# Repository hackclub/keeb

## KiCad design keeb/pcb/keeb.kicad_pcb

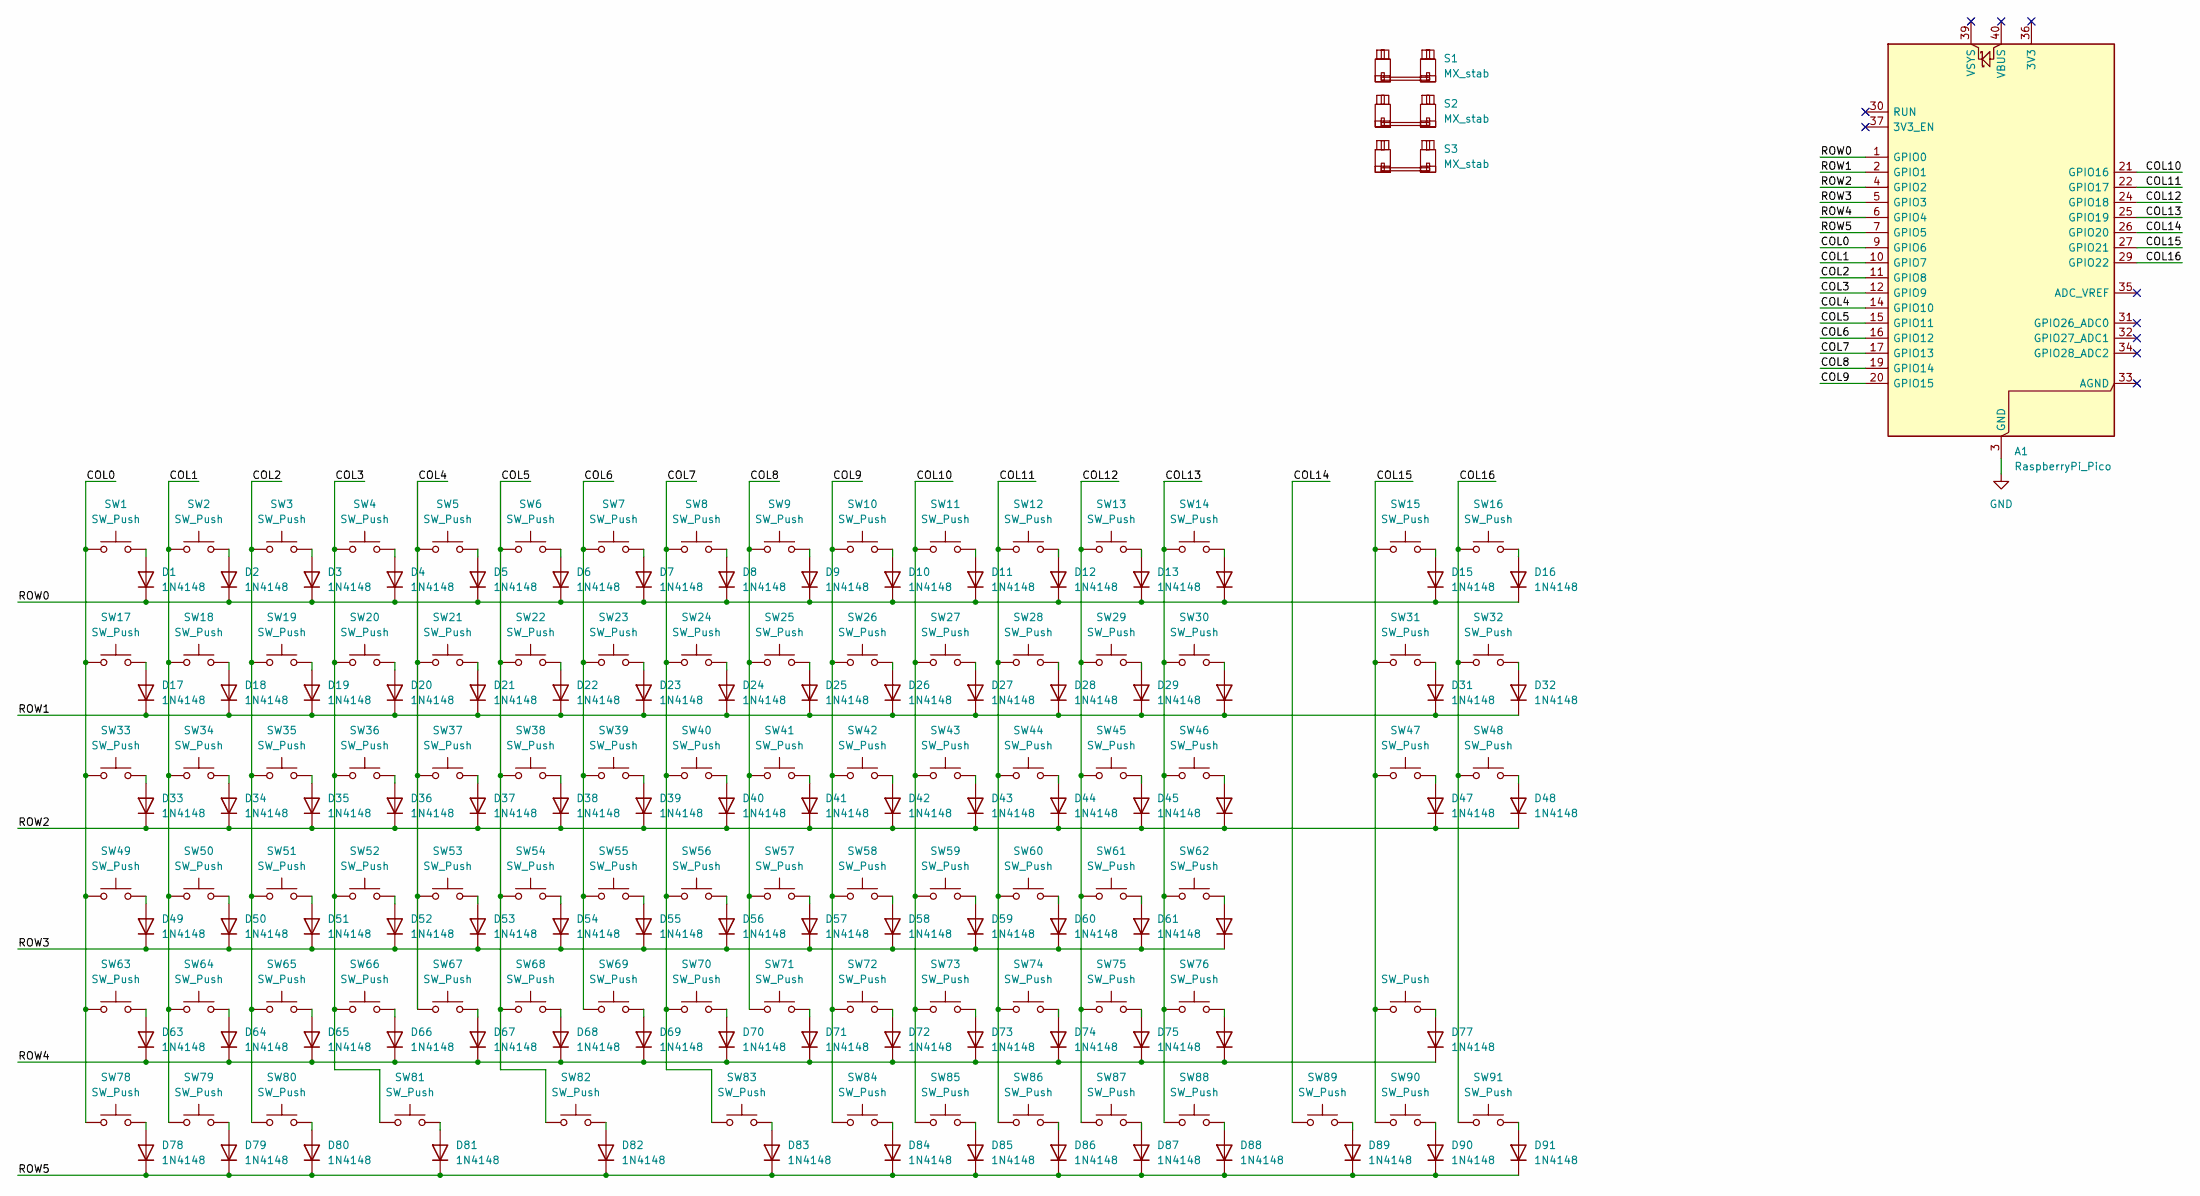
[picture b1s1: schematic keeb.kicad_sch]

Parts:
A1: RaspberryPi_Pico; RaspberryPi_Pico_Common_SMD
D1, D2, D3, D4, D5, D6, D7, D8, D9, D10, D11, D12, D13, D14, D15, D16, D17, D18, D19, D20, D21, D22, D23, D24, D25, D26, D27, D28, D29, D30, D31, D32, D33, D34, D35, D36, D37, D38, D39, D40, D41, D42, D43, D44, D45, D46, D47, D48, D49, D50, D51, D52, D53, D54, D55, D56, D57, D58, D59, D60, D61, D62, D63, D64, D65, D66, D67, D68, D69, D70, D71, D72, D73, D74, D75, D76, D77, D78, D79, D80, D81, D82, D83, D84, D85, D86, D87, D88, D89, D90, D91: 1N4148; D_DO-35_SOD27_P7.62mm_Horizontal
S1, S2, S3: MX_stab; STAB_MX_2u
SW1, SW2, SW3, SW4, SW5, SW6, SW7, SW8, SW9, SW10, SW11, SW12, SW13, SW14, SW15, SW16, SW17, SW18, SW19, SW20, SW21, SW22, SW23, SW24, SW25, SW26, SW27, SW28, SW29, SW30, SW31, SW32, SW33, SW34, SW35, SW36, SW37, SW38, SW39, SW40, SW41, SW42, SW43, SW44, SW45, SW46, SW47, SW48, SW49, SW50, SW51, SW52, SW53, SW54, SW55, SW56, SW57, SW58, SW59, SW60, SW61, SW62, SW63, SW64, SW65, SW66, SW67, SW68, SW69, SW70, SW71, SW72, SW73, SW74, SW75, SW76, SW77, SW78, SW79, SW80, SW81, SW82, SW83, SW84, SW85, SW86, SW87, SW88, SW89, SW90, SW91: SW_Push; SW_MX_1u

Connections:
/COL0: A1.9 (GPIO6), SW1.1, SW17.1, SW33.1, SW49.1, SW63.1, SW78.1
/COL1: A1.10 (GPIO7), SW2.1, SW18.1, SW34.1, SW50.1, SW64.1, SW79.1
/COL2: A1.11 (GPIO8), SW3.1, SW19.1, SW35.1, SW51.1, SW65.1, SW80.1
/COL3: A1.12 (GPIO9), SW4.1, SW20.1, SW36.1, SW52.1, SW66.1, SW81.1
/COL4: A1.14 (GPIO10), SW5.1, SW21.1, SW37.1, SW53.1, SW67.1
/COL5: A1.15 (GPIO11), SW6.1, SW22.1, SW38.1, SW54.1, SW68.1, SW82.1
/COL6: A1.16 (GPIO12), SW7.1, SW23.1, SW39.1, SW55.1, SW69.1
/COL7: A1.17 (GPIO13), SW8.1, SW24.1, SW40.1, SW56.1, SW70.1, SW83.1
/COL8: A1.19 (GPIO14), SW9.1, SW25.1, SW41.1, SW57.1, SW71.1
/COL9: A1.20 (GPIO15), SW10.1, SW26.1, SW42.1, SW58.1, SW72.1, SW84.1
/COL10: A1.21 (GPIO16), SW11.1, SW27.1, SW43.1, SW59.1, SW73.1, SW85.1
/COL11: A1.22 (GPIO17), SW12.1, SW28.1, SW44.1, SW60.1, SW74.1, SW86.1
/COL12: A1.24 (GPIO18), SW13.1, SW29.1, SW45.1, SW61.1, SW75.1, SW87.1
/COL13: A1.25 (GPIO19), SW14.1, SW30.1, SW46.1, SW62.1, SW76.1, SW88.1
/COL14: A1.26 (GPIO20), SW89.1
/COL15: A1.27 (GPIO21), SW15.1, SW31.1, SW47.1, SW77.1, SW90.1
/COL16: A1.29 (GPIO22), SW16.1, SW32.1, SW48.1, SW91.1
/ROW0: A1.1 (GPIO0), D1.1 (K), D2.1 (K), D3.1 (K), D4.1 (K), D5.1 (K), D6.1 (K), D7.1 (K), D8.1 (K), D9.1 (K), D10.1 (K), D11.1 (K), D12.1 (K), D13.1 (K), D14.1 (K), D15.1 (K), D16.1 (K)
/ROW1: A1.2 (GPIO1), D17.1 (K), D18.1 (K), D19.1 (K), D20.1 (K), D21.1 (K), D22.1 (K), D23.1 (K), D24.1 (K), D25.1 (K), D26.1 (K), D27.1 (K), D28.1 (K), D29.1 (K), D30.1 (K), D31.1 (K), D32.1 (K)
/ROW2: A1.4 (GPIO2), D33.1 (K), D34.1 (K), D35.1 (K), D36.1 (K), D37.1 (K), D38.1 (K), D39.1 (K), D40.1 (K), D41.1 (K), D42.1 (K), D43.1 (K), D44.1 (K), D45.1 (K), D46.1 (K), D47.1 (K), D48.1 (K)
/ROW3: A1.5 (GPIO3), D49.1 (K), D50.1 (K), D51.1 (K), D52.1 (K), D53.1 (K), D54.1 (K), D55.1 (K), D56.1 (K), D57.1 (K), D58.1 (K), D59.1 (K), D60.1 (K), D61.1 (K), D62.1 (K)
/ROW4: A1.6 (GPIO4), D63.1 (K), D64.1 (K), D65.1 (K), D66.1 (K), D67.1 (K), D68.1 (K), D69.1 (K), D70.1 (K), D71.1 (K), D72.1 (K), D73.1 (K), D74.1 (K), D75.1 (K), D76.1 (K), D77.1 (K)
/ROW5: A1.7 (GPIO5), D78.1 (K), D79.1 (K), D80.1 (K), D81.1 (K), D82.1 (K), D83.1 (K), D84.1 (K), D85.1 (K), D86.1 (K), D87.1 (K), D88.1 (K), D89.1 (K), D90.1 (K), D91.1 (K)
GND: A1.3 (GND), A1.8 (GND), A1.13 (GND), A1.18 (GND), A1.23 (GND), A1.28 (GND), A1.38 (GND)
unnamed: D1.2 (A), SW1.2
unnamed: D2.2 (A), SW2.2
unnamed: D3.2 (A), SW3.2
unnamed: D4.2 (A), SW4.2
unnamed: D5.2 (A), SW5.2
unnamed: D6.2 (A), SW6.2
unnamed: D7.2 (A), SW7.2
unnamed: D8.2 (A), SW8.2
unnamed: D9.2 (A), SW9.2
unnamed: D10.2 (A), SW10.2
unnamed: D11.2 (A), SW11.2
unnamed: D12.2 (A), SW12.2
unnamed: D13.2 (A), SW13.2
unnamed: D14.2 (A), SW14.2
unnamed: D15.2 (A), SW15.2
unnamed: D16.2 (A), SW16.2
unnamed: D17.2 (A), SW17.2
unnamed: D18.2 (A), SW18.2
unnamed: D19.2 (A), SW19.2
unnamed: D20.2 (A), SW20.2
unnamed: D21.2 (A), SW21.2
unnamed: D22.2 (A), SW22.2
unnamed: D23.2 (A), SW23.2
unnamed: D24.2 (A), SW24.2
unnamed: D25.2 (A), SW25.2
unnamed: D26.2 (A), SW26.2
unnamed: D27.2 (A), SW27.2
unnamed: D28.2 (A), SW28.2
unnamed: D29.2 (A), SW29.2
unnamed: D30.2 (A), SW30.2
unnamed: D31.2 (A), SW31.2
unnamed: D32.2 (A), SW32.2
unnamed: D33.2 (A), SW33.2
unnamed: D34.2 (A), SW34.2
unnamed: D35.2 (A), SW35.2
unnamed: D36.2 (A), SW36.2
unnamed: D37.2 (A), SW37.2
unnamed: D38.2 (A), SW38.2
unnamed: D39.2 (A), SW39.2
unnamed: D40.2 (A), SW40.2
unnamed: D41.2 (A), SW41.2
unnamed: D42.2 (A), SW42.2
unnamed: D43.2 (A), SW43.2
unnamed: D44.2 (A), SW44.2
unnamed: D45.2 (A), SW45.2
unnamed: D46.2 (A), SW46.2
unnamed: D47.2 (A), SW47.2
unnamed: D48.2 (A), SW48.2
unnamed: D49.2 (A), SW49.2
unnamed: D50.2 (A), SW50.2
unnamed: D51.2 (A), SW51.2
unnamed: D52.2 (A), SW52.2
unnamed: D53.2 (A), SW53.2
unnamed: D54.2 (A), SW54.2
unnamed: D55.2 (A), SW55.2
unnamed: D56.2 (A), SW56.2
unnamed: D57.2 (A), SW57.2
unnamed: D58.2 (A), SW58.2
unnamed: D59.2 (A), SW59.2
unnamed: D60.2 (A), SW60.2
unnamed: D61.2 (A), SW61.2
unnamed: D62.2 (A), SW62.2
unnamed: D63.2 (A), SW63.2
unnamed: D64.2 (A), SW64.2
unnamed: D65.2 (A), SW65.2
unnamed: D66.2 (A), SW66.2
unnamed: D67.2 (A), SW67.2
unnamed: D68.2 (A), SW68.2
unnamed: D69.2 (A), SW69.2
unnamed: D70.2 (A), SW70.2
unnamed: D71.2 (A), SW71.2
unnamed: D72.2 (A), SW72.2
unnamed: D73.2 (A), SW73.2
unnamed: D74.2 (A), SW74.2
unnamed: D75.2 (A), SW75.2
unnamed: D76.2 (A), SW76.2
unnamed: D77.2 (A), SW77.2
unnamed: D78.2 (A), SW78.2
unnamed: D79.2 (A), SW79.2
unnamed: D80.2 (A), SW80.2
unnamed: D81.2 (A), SW81.2
unnamed: D82.2 (A), SW82.2
unnamed: D83.2 (A), SW83.2
unnamed: D84.2 (A), SW84.2
unnamed: D85.2 (A), SW85.2
unnamed: D86.2 (A), SW86.2
unnamed: D87.2 (A), SW87.2
unnamed: D88.2 (A), SW88.2
unnamed: D89.2 (A), SW89.2
unnamed: D90.2 (A), SW90.2
unnamed: D91.2 (A), SW91.2

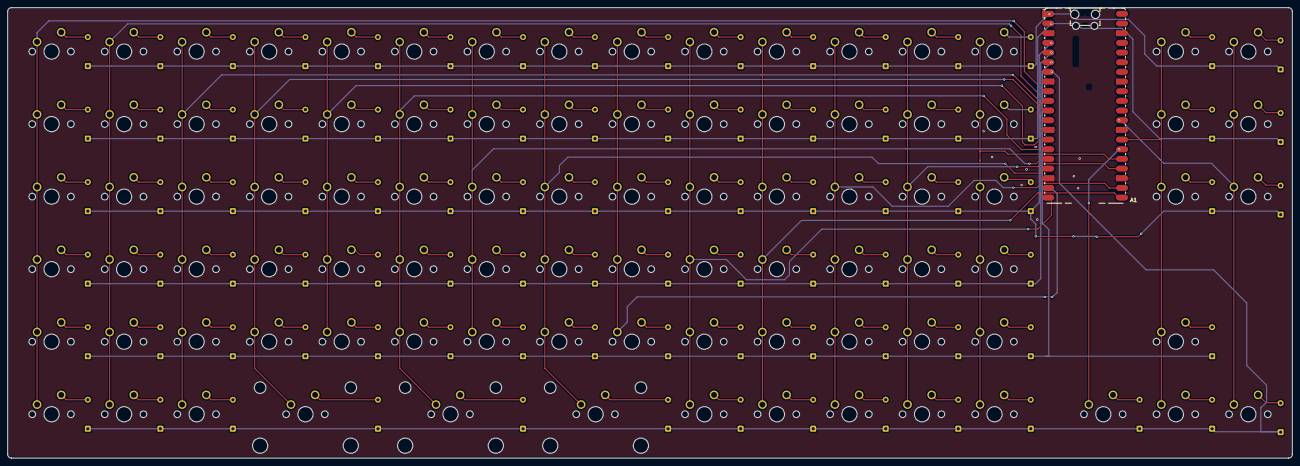
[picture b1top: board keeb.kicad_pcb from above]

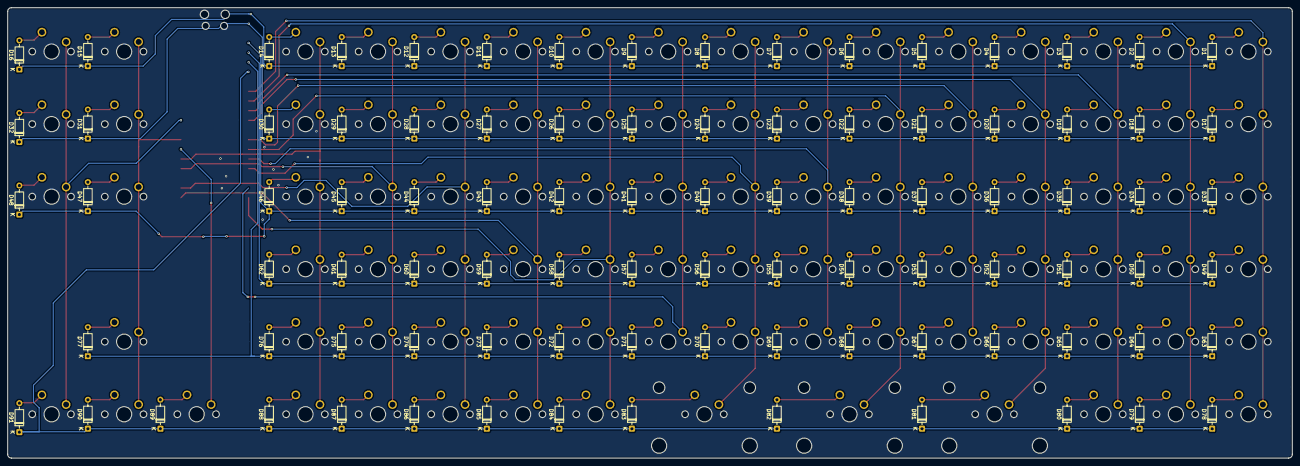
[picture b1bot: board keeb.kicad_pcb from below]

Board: 2 copper layers, 337.4 x 118.3 mm, 186 parts (91 on the bottom side), 115 nets.

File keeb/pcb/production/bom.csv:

Designator,Footprint,Quantity,Value,LCSC Part #
A1,RaspberryPi_Pico_Common_SMD,1,RaspberryPi_Pico,
"D1, D10, D11, D12, D13, D14, D15, D16, D17, D18, D19, D2, D20, D21, D22, D23, D24, D25, D26, D27, D28, D29, D3, D30, D31, D32, D33, D34, D35, D36, D37, D38, D39, D4, D40, D41, D42, D43, D44, D45, D46, D47, D48, D49, D5, D50, D51, D52, D53, D54, D55, D56, D57, D58, D59, D6, D60, D61, D62, D63, D64, D65, D66, D67, D68, D69, D7, D70, D71, D72, D73, D74, D75, D76, D77, D78, D79, D8, D80, D81, D82, D83, D84, D85, D86, D87, D88, D89, D9, D90, D91",D_DO-35_SOD27_P7.62mm_Horizontal,91,1N4148,
"S1, S2, S3",STAB_MX_2u,3,MX_stab,
"SW1, SW10, SW11, SW12, SW13, SW14, SW15, SW16, SW17, SW18, SW19, SW2, SW20, SW21, SW22, SW23, SW24, SW25, SW26, SW27, SW28, SW29, SW3, SW30, SW31, SW32, SW33, SW34, SW35, SW36, SW37, SW38, SW39, SW4, SW40, SW41, SW42, SW43, SW44, SW45, SW46, SW47, SW48, SW49, SW5, SW50, SW51, SW52, SW53, SW54, SW55, SW56, SW57, SW58, SW59, SW6, SW60, SW61, SW62, SW63, SW64, SW65, SW66, SW67, SW68, SW69, SW7, SW70, SW71, SW72, SW73, SW74, SW75, SW76, SW77, SW78, SW79, SW8, SW80, SW81, SW82, SW83, SW84, SW85, SW86, SW87, SW88, SW89, SW9, SW90, SW91",SW_MX_1u,91,SW_Push,

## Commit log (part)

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2026-04-04 Bump defu from 6.1.4 to 6.1.6
    Bumps [defu](https://github.com/unjs/defu) from 6.1.4 to 6.1.6.
    - [Release notes](https://github.com/unjs/defu/releases)
    - [Changelog](https://github.com/unjs/defu/blob/main/CHANGELOG.md)
    - [Commits](https://github.com/unjs/defu/compare/v6.1.4...v6.1.6)
    ---
    updated-dependencies:
2026-04-07 Bump vite from 7.3.1 to 7.3.2
    Bumps [vite](https://github.com/vitejs/vite/tree/HEAD/packages/vite) from 7.3.1 to 7.3.2.
    - [Release notes](https://github.com/vitejs/vite/releases)
    - [Changelog](https://github.com/vitejs/vite/blob/v7.3.2/packages/vite/CHANGELOG.md)
    - [Commits](https://github.com/vitejs/vite/commits/v7.3.2/packages/vite)
    ---
    updated-dependencies:
2026-04-13 added stuff
2026-04-14 polish homepage: new fonts, OKLCH palette, FAQ section, refined layout
2026-04-14 Added the docs and some other things
2026-04-14 added a dockerfile
2026-04-21 Bump astro from 6.1.1 to 6.1.6
    Bumps [astro](https://github.com/withastro/astro/tree/HEAD/packages/astro) from 6.1.1 to 6.1.6.
    - [Release notes](https://github.com/withastro/astro/releases)
    - [Changelog](https://github.com/withastro/astro/blob/main/packages/astro/CHANGELOG.md)
    - [Commits](https://github.com/withastro/astro/commits/astro@6.1.6/packages/astro)
    ---
    updated-dependencies:
2026-05-13 Bump astro from 6.1.1 to 6.1.10
    Bumps [astro](https://github.com/withastro/astro/tree/HEAD/packages/astro) from 6.1.1 to 6.1.10.
    - [Release notes](https://github.com/withastro/astro/releases)
    - [Changelog](https://github.com/withastro/astro/blob/main/packages/astro/CHANGELOG.md)
    - [Commits](https://github.com/withastro/astro/commits/astro@6.1.10/packages/astro)
    ---
    updated-dependencies:
2026-05-14 Bump devalue from 5.6.4 to 5.8.1
    Bumps [devalue](https://github.com/sveltejs/devalue) from 5.6.4 to 5.8.1.
    - [Release notes](https://github.com/sveltejs/devalue/releases)
    - [Changelog](https://github.com/sveltejs/devalue/blob/main/CHANGELOG.md)
    - [Commits](https://github.com/sveltejs/devalue/compare/v5.6.4...v5.8.1)
    ---
    updated-dependencies:
2026-05-24 reorganized design files
2026-05-24 added firmware
2026-05-24 forgot to close kicad
2026-05-24 Bump postcss from 8.5.8 to 8.5.15
    Bumps [postcss](https://github.com/postcss/postcss) from 8.5.8 to 8.5.15.
    - [Release notes](https://github.com/postcss/postcss/releases)
    - [Changelog](https://github.com/postcss/postcss/blob/main/CHANGELOG.md)
    - [Commits](https://github.com/postcss/postcss/compare/8.5.8...8.5.15)
    ---
    updated-dependencies:
2026-05-27 Fixed change
2026-05-27 Change design tool from Fusion to Onshape
    Updated the documentation to reflect the use of Onshape instead of Fusion for designing a 3D-printable keyboard case.
2026-05-27 Specify maximum case dimensions for 3D printing
    Added a size constraint for the case design to ensure printability.
2026-05-27 Fixed Dockerfile
2026-05-27 Changed the theme os the YSWS
2026-05-27 reverted
2026-05-27 Update hero subtitle to encourage personalization
2026-05-27 Refine hero section text for clarity
2026-05-27 Clean up case design documentation header
    Removed unnecessary header from the case design documentation.
2026-05-27 Clean up formatting in case-design.md
    Remove unnecessary line breaks in case-design.md
2026-05-28 Updated frontpage picture
2026-06-01 Changes purple to red in the keyboard visual component and updates the favicon to match the new color scheme.
2026-06-01 fix: update purple color scheme
2026-06-01 added logo
2026-06-01 test to add images to the hero section
2026-06-01 adding images to hero
2026-06-01 moving photos
2026-06-01 add more photos and de-vibecode
2026-06-01 photo updates
2026-06-01 smaller image
2026-06-01 image
2026-06-01 updated fonts
2026-06-01 font issues
2026-06-02 Added falling Keys as decoration
2026-06-02 adjusted keys and moved dcumentation titles down
2026-06-02 adjust sidebar position and update nav link; modify padding in layout and scale effect on index page
2026-06-02 fixed
2026-06-02 fixed cut off key caps
2026-06-02 Changed wording of getting started and case design docs, added a new image for the falling keys image,and updated the image.
2026-06-02 fixed grpahics blocking words
2026-06-02 fixed images blocking text again
2026-06-02 updated logo
2026-06-02 submission form
2026-06-02 fixed kit
2026-06-02 fiex: update kit contents
2026-06-02 fixed more u=issues with kit
2026-06-02 updated link in kit
2026-06-02 fixed git hub button and links
2026-06-02 removed more github buttons
2026-06-04 github repo explanation
2026-06-04 fixed best
2026-06-04 added more to the submission page
2026-06-04 Fixed redirecting issue
2026-06-04 fixed next steps in getting started
2026-06-04 B Better PCB design documentation. Added more details and examples to help users understand the concepts and best practices for designing printed circuit boards. This will improve the overall quality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
2026-06-05 Better wiring photos
2026-06-05 fixed wording around keycaps
2026-06-05 Added clearer instuctions for PCB design.
2026-06-05 Changed instructions
2026-06-06 Update getting started guide for clarity and detail
2026-06-06 Clarify repo journaling instructions
    Updated wording for clarity on project verification and tracking.
2026-06-06 Ignore PCB backups and remove keeb-backups
    .
2026-06-06 added blender
2026-06-08 More info for begginers
2026-06-08 removed bad spelling
2026-06-08 easier to tell that they are dropdowns
2026-06-08 fixed gloassary
2026-06-08 updated lapse
2026-06-08 updated instructions
2026-06-08 more instructions
2026-06-08 fixed image
2026-06-08 fixed double getting started page
2026-06-16 Create shop page
2026-06-16 Made The basic structure of the shop
2026-06-16 feat(keeb): add Airtable rewards system and shop redesign
2026-06-16 feat(keeb): add reviewer access gate for shop preview
2026-06-18 fixed instructions
2026-06-18 Bump astro from 6.4.4 to 6.4.6
    Bumps [astro](https://github.com/withastro/astro/tree/HEAD/packages/astro) from 6.4.4 to 6.4.6.
    - [Release notes](https://github.com/withastro/astro/releases)
    - [Changelog](https://github.com/withastro/astro/blob/main/packages/astro/CHANGELOG.md)
    - [Commits](https://github.com/withastro/astro/commits/astro@6.4.6/packages/astro)
    ---
    updated-dependencies:
2026-06-30 Major updates for all information and fixed shop
2026-06-30 Bump esbuild and astro
    Bumps [esbuild](https://github.com/evanw/esbuild) to 0.28.1 and updates ancestor dependency [astro](https://github.com/withastro/astro/tree/HEAD/packages/astro). These dependencies need to be updated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
    Updates `esbuild` from 0.27.7 to 0.28.1
    - [Release notes](https://github.com/evanw/esbuild/releases)
    - [Changelog](https://github.com/evanw/esbuild/blob/main/CHANGELOG.md)
    - [Commits](https://github.com/evanw/esbuild/compare/v0.27.7...v0.28.1)
    Updates `astro` from 6.4.8 to 7.0.4
